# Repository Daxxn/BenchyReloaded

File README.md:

# BENCHY Version 2 - A Whole New Benchy Boi

>Alot of this is old and needs to be updated!

Your electronics workbench buddy! (Warning - Benchy is not actually your buddy and will probably try to kill you. It's hideously expensive, and way too time consuming to build!)

## Features

- Single Board Computer running embedded linux
- 5 Port USB 3.1 hub
- All data ports are **properly** protected agains over-current and backfeeding
- 2 USB 2.0 ports for the SBC peripherals (keyboard/mouse)
- 2 1Gb Ethernet ports
- 8 Software controlled relays for general things like lighting
- (In Development) Lab Power Supply W/ Current or Voltage Limiting (15V @ 2A)
- Lighting system that can drive 4 RGBW, 2 RGB, 6 dimmable, and 4 switched LED strips
- Electronic Load (5A Max)
- Simple 8 channel volt meter for quick and easy voltage testing
- (in development) Simple LCR Meter
- (in development) Function Generator

# Complete Assembly

## Motherboard Processor

This design integrates an STM32MP1 Series micro processor (U2) with 8Gb DDR3 memory (U20). This adds a large amount of raw power internally. Taking alot of the load required to control the sub-systems from the users PC and adds more flexability to the system as a whole.

## USB Hub

The main reason why I needed to design my own USB hub instead of stuffing an "off the shelf" hub up benchys trumpet was the absolute lack of protection circuitry in most "consumer grade" USB hubs. There is no back-feed protection, verry little to no current monitoring, and the bare minimum ESD and EMI protection. Thats just not acceptable! imagine my supprise when I cracked open an $85 hub from Amazon and, after blowing out a channel, found no power management at all. The cost of finding a hub that has these protections is going to be around the same price as designing and building my own. (Except for the time investment... but who cares about that?!?)

These features arent exaclty flashy, they dont look very good on a brochure. So they usually arent there. If they are, its just a bullet point. Often they just _claim_ to conform to the USB spec. The lack protection doesn't actually conform to the spec at all. I will admit, some of the protection features are optional and not necessary for every day use. The problem is an electronics workbench is very mean. It will bully these simple hubs until they don't want to play along anymore.

## I2C Bus

Im using a quite extensive I2C bus system to communicate with the different boards and functional blocks. This cuts WAY down on the number of wires and pins required for the main controller and allows for better modularity within benchy.

Due to the size of the bus and the different devices, the bus is split by an I2C Mux to keep bus integrity while communicating to far PCBs.

# Power Supply

The one thing that made the two different power supplies possible was the Switch-Mode Power Supply (SMPS) that was built into the DVR box that spawned this project. The output from the SMPS is a high-current 12V source and 30V source. This was easy to adapt to my needs.

## Adjustable supply

- 15v @ 2A
- Controlled from the motherboard or front panel

The adjustable supply is built with help from [Dave, (Thanks Dave!)](https://www.youtube.com/watch?v=CIGjActDeoM&list=PLBF35875F73B5C9B5&index=1&ab_channel=EEVblog) using the [LM317](https://rocelec.widen.net/view/pdf/mlzstqhekh/slvs044x.pdf?t.download=true&u=5oefqw) adjustable regulator.

## 5V Supply

The ATX supply can provide 15 amps to the USB ports allowing each port to supply around 2 amps. Power is managed by the [UCS2114s.](https://ww1.microchip.com/downloads/aemDocuments/documents/APID/ProductDocuments/DataSheets/UCS2114-Data-Sheet-20005743B.pdf) Controlling both the current limit and backfeeding.

# Electronic Load

Fairly standard design using a MOSFET in its linear region, dissipating alot of energy. With the help of a big heatsink and a fan, it can be used to load power supplies to test their response. The current shunt will allow for precise measurement of power usage. Control is linked to the main microcontroller on the the motherboard. Allowing full control.

# 8 Channel Volt Meter

Low voltage volt meters with moderate accuracy and speed. Designed to measure multiple voltage levels simultaneously. This is helpful for testing power supplies designed for advanced ICs that require lots of voltages to run. Such as Processors, FPGAs, and PC Motherboards.

# Function generator

Creates sine, square, and triangle waves. from ~100Hz to ~100KHz.

# 8 Mains Rated Relays

8 channel relay block used to control general things around the bench like lighting and other small devices. Rated for mains voltage but not for high current.

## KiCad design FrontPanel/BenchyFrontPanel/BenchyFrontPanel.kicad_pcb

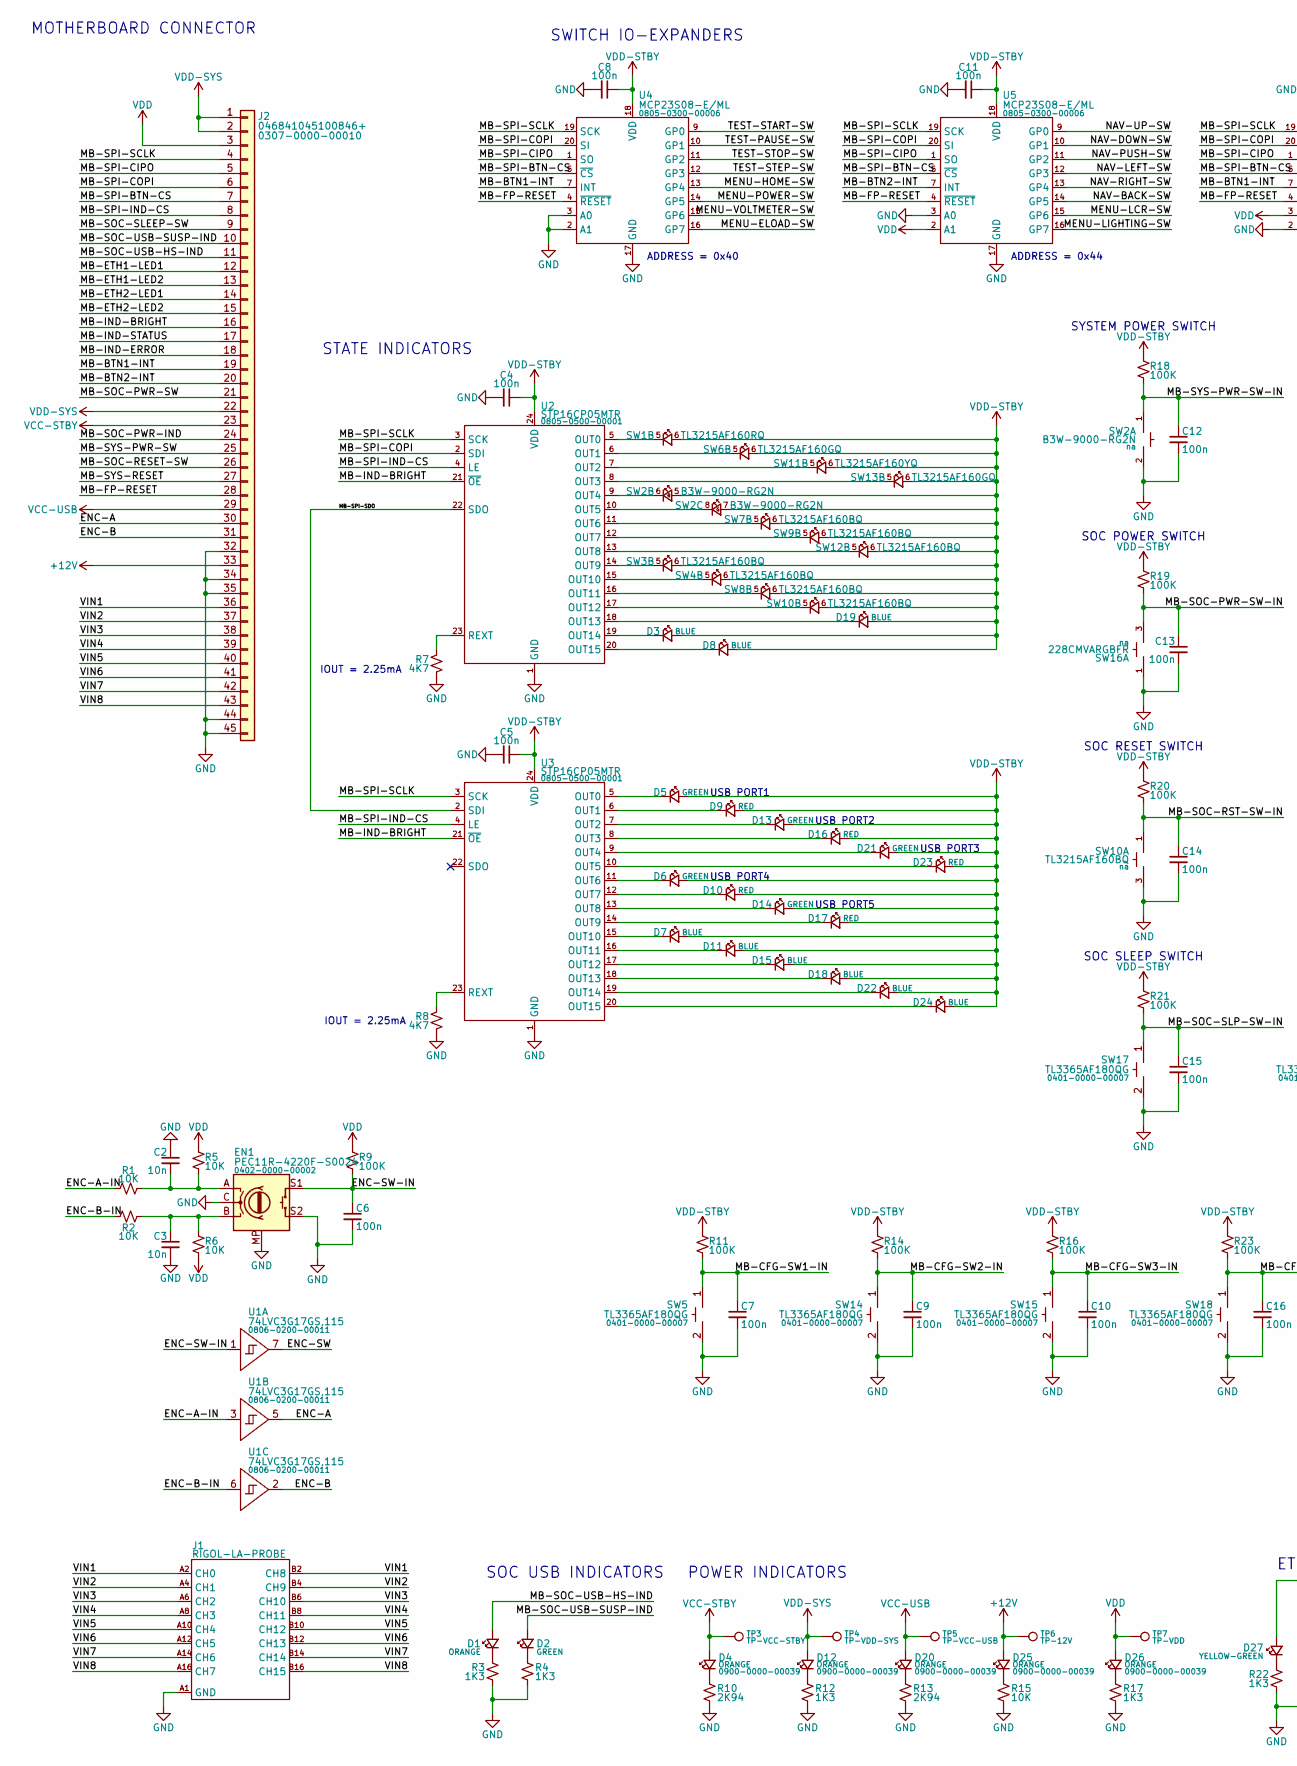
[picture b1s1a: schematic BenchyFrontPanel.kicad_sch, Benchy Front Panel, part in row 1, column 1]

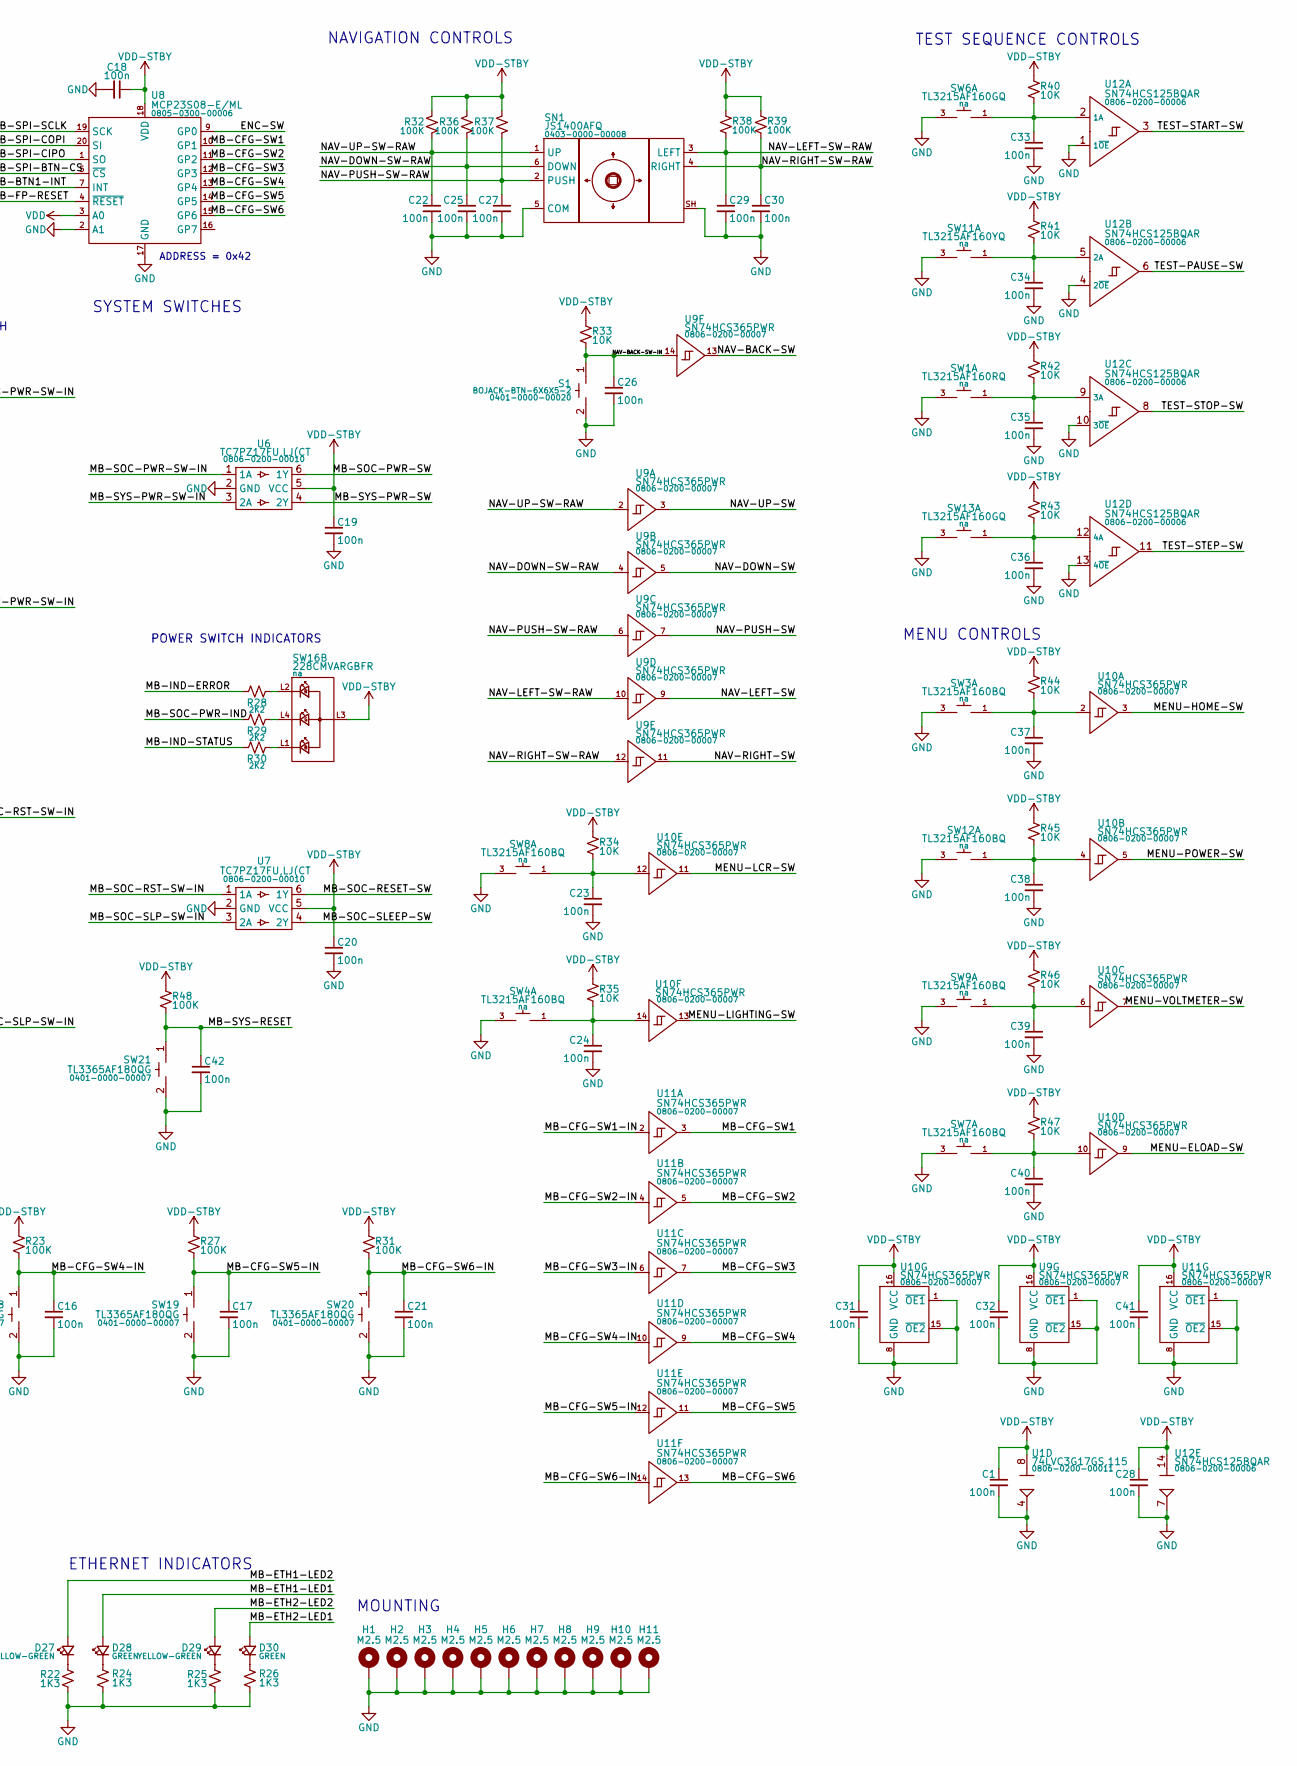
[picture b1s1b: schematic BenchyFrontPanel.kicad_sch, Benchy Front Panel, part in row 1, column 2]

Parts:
C1, C4, C5, C6, C7, C8, C9, C10, C11, C12, C13, C14, C15, C16, C17, C18, C19, C20, C21, C22, C23, C24, C25, C26, C27, C28, C29, C30, C31, C32, C33, C34, C35, C36, C37, C38, C39, C40, C41, C42: 100n; CAP_0402; PartNumber 0201-0100-00086
C2, C3: 10n; CAP_0402; PartNumber 0201-0100-00031
D1, D4, D12, D20, D25, D26: CZ3-0603-ORANGE; LED_0603_1608Metric; PartNumber 0900-0000-00039
D2, D5, D6, D13, D14, D21, D28, D30: CZ2-0603-GREEN; LED_0603_1608Metric; PartNumber 0900-0000-00038
D3, D7, D8, D11, D15, D18, D19, D22, D24: CZ1-0603-BLUE; LED_0603_1608Metric; PartNumber 0900-0000-00037
D9, D10, D16, D17, D23: CZ5-0603-RED; LED_0603_1608Metric; PartNumber 0900-0000-00041
D27, D29: CZ8-0603-YLW-GREEN; LED_0603_1608Metric; PartNumber 0900-0000-00044
EN1: PEC11R-4220F-S0024; PEC11R; PartNumber 0402-0000-00002
H1, H2, H3, H4, H5, H6, H7, H8, H9, H10, H11: M2.5; MountingHole_2.7mm_M2.5_ISO7380_Pad
J1: RIGOL-LA-PROBE; 10018784-10200TLF; PartNumber na
J2: 046841045100846+; PartNumber 0307-0000-00010
R1, R2, R5, R6, R15, R33, R34, R35, R40, R41, R42, R43, R44, R45, R46, R47: 10K; RES_0402; PartNumber 0204-0000-00016
R3, R4, R12, R17, R22, R24, R25, R26: 1K3; RES_0402; PartNumber 0204-0000-00004
R7, R8: 4K7; RES_0402; PartNumber 0204-0000-00068
R9, R11, R14, R16, R18, R19, R20, R21, R23, R27, R31, R32, R36, R37, R38, R39, R48: 100K; RES_0402; PartNumber 0204-0000-00013
R10, R13: 2K94; RES_0402; PartNumber 0204-0000-00039
R28, R29, R30: 2K2; RES_0402; PartNumber 0204-0000-00033
S1: BOJACK-BTN-6X6X5-2; BOJACK-BTN-6x6x5; PartNumber 0401-0000-00020
SN1: JS1400AFQ; JS1400; PartNumber 0403-0000-00008
SW1: TL3215AF160RQ; TL3215A; PartNumber na
SW2: B3W-9000-RG2N; B3W-9000; PartNumber na
SW3, SW4, SW7, SW8, SW9, SW10, SW12: TL3215AF160BQ; TL3215A; PartNumber na
SW5, SW14, SW15, SW17, SW18, SW19, SW20, SW21: TL3365AF180QG; PartNumber 0401-0000-00007
SW6, SW13: TL3215AF160GQ; TL3215A; PartNumber na
SW11: TL3215AF160YQ; TL3215A; PartNumber na
SW16: 228CMVARGBFR; 228C; PartNumber na
TP3: TP-VCC-STBY; TestPoint_Pad_D2.0mm; PartNumber na
TP4: TP-VDD-SYS; TestPoint_Pad_D2.0mm; PartNumber na
TP5: TP-VCC-USB; TestPoint_Pad_D2.0mm; PartNumber na
TP6: TP-12V; TestPoint_Pad_D2.0mm; PartNumber na
TP7: TP-VDD; TestPoint_Pad_D2.0mm; PartNumber na
U1: 74LVC3G17GS,115; X2SON-8_1.4x1mm_P0.35mm; PartNumber 0806-0200-00011
U2, U3: STP16CP05MTR; SOIC-24W_7.5x15.4mm_P1.27mm; PartNumber 0805-0500-00001
U4, U5, U8: MCP23S08-E/ML; QFN-20-1EP_4x4mm_P0.5mm_EP2.7x2.7mm; PartNumber 0805-0300-00006
U6, U7: TC7PZ17FU,LJ(CT; SOT-363_SC-70-6; PartNumber 0806-0200-00010
U9, U10, U11: SN74HCS365PWR; TSSOP-16_4.4x5mm_P0.65mm; PartNumber 0806-0200-00007
U12: SN74HCS125BQAR; WQFN-14_B3x2.5mm_P0.5mm; PartNumber 0806-0200-00006

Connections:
+12V: D25.2 (A), J2.33, TP6.1 (TP)
/ENC-A: J2.30, U1.5 (2Y)
/ENC-A-IN: R1.1, U1.3 (2A)
/ENC-B: J2.31, U1.2 (3Y)
/ENC-B-IN: R2.1, U1.6 (3A)
/ENC-SW: U1.7 (1Y), U8.9 (GP0)
/ENC-SW-IN: C6.1, EN1.S1, R9.2, U1.1 (1A)
/MB-BTN1-INT: J2.19, U4.7 (INT), U8.7 (INT)
/MB-BTN2-INT: J2.20, U5.7 (INT)
/MB-CFG-SW1: U8.10 (GP1), U11.3 (Y1)
/MB-CFG-SW1-IN: C7.1, R11.2, SW5.1, U11.2 (A1)
/MB-CFG-SW2: U8.11 (GP2), U11.5 (Y2)
/MB-CFG-SW2-IN: C9.1, R14.2, SW14.1, U11.4 (A2)
/MB-CFG-SW3: U8.12 (GP3), U11.7 (Y3)
/MB-CFG-SW3-IN: C10.1, R16.2, SW15.1, U11.6 (A3)
/MB-CFG-SW4: U8.13 (GP4), U11.9 (Y4)
/MB-CFG-SW4-IN: C16.1, R23.2, SW18.1, U11.10 (A4)
/MB-CFG-SW5: U8.14 (GP5), U11.11 (Y5)
/MB-CFG-SW5-IN: C17.1, R27.2, SW19.1, U11.12 (A5)
/MB-CFG-SW6: U8.15 (GP6), U11.13 (Y6)
/MB-CFG-SW6-IN: C21.1, R31.2, SW20.1, U11.14 (A6)
/MB-ETH1-LED1: D28.2 (A), J2.12
/MB-ETH1-LED2: D27.2 (A), J2.13
/MB-ETH2-LED1: D30.2 (A), J2.14
/MB-ETH2-LED2: D29.2 (A), J2.15
/MB-FP-RESET: J2.28, U4.4 (~RESET), U5.4 (~RESET), U8.4 (~RESET)
/MB-IND-BRIGHT: J2.16, U2.21 (~OE), U3.21 (~OE)
/MB-IND-ERROR: J2.18, R28.1
/MB-IND-STATUS: J2.17, R30.1
/MB-SOC-PWR-IND: J2.24, R29.1
/MB-SOC-PWR-SW: J2.21, U6.6 (1Y)
/MB-SOC-PWR-SW-IN: C13.1, R19.2, SW16.3 (SWB), SW16.4 (SWB), U6.1 (1A)
/MB-SOC-RESET-SW: J2.26, U7.6 (1Y)
/MB-SOC-RST-SW-IN: C14.1, R20.2, SW10.1 (SWA), SW10.2 (SWA), U7.1 (1A)
/MB-SOC-SLEEP-SW: J2.9, U7.4 (2Y)
/MB-SOC-SLP-SW-IN: C15.1, R21.2, SW17.1, U7.3 (2A)
/MB-SOC-USB-HS-IND: D1.2 (A), J2.11
/MB-SOC-USB-SUSP-IND: D2.2 (A), J2.10
/MB-SPI-BTN-CS: J2.7, U4.5 (~CS), U5.5 (~CS), U8.5 (~CS)
/MB-SPI-CIPO: J2.5, U4.1 (SO), U5.1 (SO), U8.1 (SO)
/MB-SPI-COPI: J2.6, U2.2 (SDI), U4.20 (SI), U5.20 (SI), U8.20 (SI)
/MB-SPI-IND-CS: J2.8, U2.4 (LE), U3.4 (LE)
/MB-SPI-SCLK: J2.4, U2.3 (SCK), U3.3 (SCK), U4.19 (SCK), U5.19 (SCK), U8.19 (SCK)
/MB-SPI-SDO: U2.22 (SDO), U3.2 (SDI)
/MB-SYS-PWR-SW: J2.25, U6.4 (2Y)
/MB-SYS-PWR-SW-IN: C12.1, R18.2, SW2.1 (SWA), SW2.3 (SWA), U6.3 (2A)
/MB-SYS-RESET: C42.1, J2.27, R48.2, SW21.1
/MENU-ELOAD-SW: U4.16 (GP7), U10.9 (Y4)
/MENU-HOME-SW: U4.13 (GP4), U10.3 (Y1)
/MENU-LCR-SW: U5.15 (GP6), U10.11 (Y5)
/MENU-LIGHTING-SW: U5.16 (GP7), U10.13 (Y6)
/MENU-POWER-SW: U4.14 (GP5), U10.5 (Y2)
/MENU-VOLTMETER-SW: U4.15 (GP6), U10.7 (Y3)
/NAV-BACK-SW: U5.14 (GP5), U9.13 (Y6)
/NAV-BACK-SW-IN: C26.1, R33.2, S1.1, U9.14 (A6)
/NAV-DOWN-SW: U5.10 (GP1), U9.5 (Y2)
/NAV-DOWN-SW-RAW: C25.1, R36.2, SN1.6 (DOWN), U9.4 (A2)
/NAV-LEFT-SW: U5.12 (GP3), U9.9 (Y4)
/NAV-LEFT-SW-RAW: C29.1, R38.2, SN1.3 (LEFT), U9.10 (A4)
/NAV-PUSH-SW: U5.11 (GP2), U9.7 (Y3)
/NAV-PUSH-SW-RAW: C27.1, R37.2, SN1.2 (PUSH), U9.6 (A3)
/NAV-RIGHT-SW: U5.13 (GP4), U9.11 (Y5)
/NAV-RIGHT-SW-RAW: C30.1, R39.2, SN1.4 (RIGHT), U9.12 (A5)
/NAV-UP-SW: U5.9 (GP0), U9.3 (Y1)
/NAV-UP-SW-RAW: C22.1, R32.2, SN1.1 (UP), U9.2 (A1)
/TEST-PAUSE-SW: U4.10 (GP1), U12.6 (2Y)
/TEST-START-SW: U4.9 (GP0), U12.3 (1Y)
/TEST-STEP-SW: U4.12 (GP3), U12.11 (4Y)
/TEST-STOP-SW: U4.11 (GP2), U12.8 (3Y)
/VIN1: J1.A2 (CH0), J1.B2 (CH8), J2.36
/VIN2: J1.A4 (CH1), J1.B4 (CH9), J2.37
/VIN3: J1.A6 (CH2), J1.B6 (CH10), J2.38
/VIN4: J1.A8 (CH3), J1.B8 (CH11), J2.39
/VIN5: J1.A10 (CH4), J1.B10 (CH12), J2.40
/VIN6: J1.A12 (CH5), J1.B12 (CH13), J2.41
/VIN7: J1.A14 (CH6), J1.B14 (CH14), J2.42
/VIN8: J1.A16 (CH7), J1.B16 (CH15), J2.43
GND: C1.2, C2.1, C3.2, C4.2, C5.2, C6.2, C7.2, C8.2, C9.2, C10.2, C11.2, C12.2, C13.2, C14.2, C15.2, C16.2, C17.2, C18.2, C19.2, C20.2, C21.2, C22.2, C23.2, C24.2, C25.2, C26.2, C27.2, C28.2, C29.2, C30.2, C31.2, C32.2, C33.2, C34.2, C35.2, C36.2, C37.2, C38.2, C39.2, C40.2, C41.2, C42.2, EN1.C, EN1.MP, EN1.S2, H1.1, H2.1, H3.1, H4.1, H5.1, H6.1, H7.1, H8.1, H9.1, H10.1, H11.1, J1.A1 (GND), J1.A3 (GND), J1.A5 (GND), J1.A7 (GND), J1.A9 (GND), J1.A11 (GND), J1.A13 (GND), J1.A15 (GND), J1.A17 (GND), J1.A18 (GND), J1.B1 (GND), J1.B3 (GND), J1.B5 (GND), J1.B7 (GND), J1.B9 (GND), J1.B11 (GND), J1.B13 (GND), J1.B15 (GND), J1.B17 (GND), J1.B18 (GND), J2.32, J2.34, J2.35, J2.44, J2.45, R3.2, R4.2, R7.2, R8.2, R10.2, R12.2, R13.2, R15.2, R17.2, R22.2, R24.2, R25.2, R26.2, S1.2, SN1.5 (COM), SN1.SH, SW1.3 (SWB), SW1.4 (SWB), SW2.2 (SWB), SW2.4 (SWB), SW3.3 (SWB), SW3.4 (SWB), SW4.3 (SWB), SW4.4 (SWB), SW5.2, SW6.3 (SWB), SW6.4 (SWB), SW7.3 (SWB), SW7.4 (SWB), SW8.3 (SWB), SW8.4 (SWB), SW9.3 (SWB), SW9.4 (SWB), SW10.3 (SWB), SW10.4 (SWB), SW11.3 (SWB), SW11.4 (SWB), SW12.3 (SWB), SW12.4 (SWB), SW13.3 (SWB), SW13.4 (SWB), SW14.2, SW15.2, SW16.1 (SWA), SW16.2 (SWA), SW17.2, SW18.2, SW19.2, SW20.2, SW21.2, U1.4 (GND), U2.1 (GND), U3.1 (GND), U4.2 (A1), U4.3 (A0), U4.17 (GND), U4.21 (GND), U5.3 (A0), U5.17 (GND), U5.21 (GND), U6.2 (GND), U7.2 (GND), U8.2 (A1), U8.17 (GND), U8.21 (GND), U9.1 (~OE1), U9.8 (GND), U9.15 (~OE2), U10.1 (~OE1), U10.8 (GND), U10.15 (~OE2), U11.1 (~OE1), U11.8 (GND), U11.15 (~OE2), U12.1 (1~OE), U12.4 (2~OE), U12.7 (GND), U12.10 (3~OE), U12.13 (4~OE), U12.15 (GND)
unnamed: C2.2, EN1.A, R1.2, R5.2
unnamed: C3.1, EN1.B, R2.2, R6.1
unnamed: D1.1 (K), R3.1
unnamed: D2.1 (K), R4.1
unnamed: D3.1 (K), U2.19 (OUT14)
unnamed: D4.1 (K), R10.1
unnamed: D5.1 (K), U3.5 (OUT0)
unnamed: D6.1 (K), U3.11 (OUT6)
unnamed: D7.1 (K), U3.15 (OUT10)
unnamed: D8.1 (K), U2.20 (OUT15)
unnamed: D9.1 (K), U3.6 (OUT1)
unnamed: D10.1 (K), U3.12 (OUT7)
unnamed: D11.1 (K), U3.16 (OUT11)
unnamed: D12.1 (K), R12.1
unnamed: D13.1 (K), U3.7 (OUT2)
unnamed: D14.1 (K), U3.13 (OUT8)
unnamed: D15.1 (K), U3.17 (OUT12)
unnamed: D16.1 (K), U3.8 (OUT3)
unnamed: D17.1 (K), U3.14 (OUT9)
unnamed: D18.1 (K), U3.18 (OUT13)
unnamed: D19.1 (K), U2.18 (OUT13)
unnamed: D20.1 (K), R13.1
unnamed: D21.1 (K), U3.9 (OUT4)
unnamed: D22.1 (K), U3.19 (OUT14)
unnamed: D23.1 (K), U3.10 (OUT5)
unnamed: D24.1 (K), U3.20 (OUT15)
unnamed: D25.1 (K), R15.1
unnamed: D26.1 (K), R17.1
unnamed: D27.1 (K), R22.1
unnamed: D28.1 (K), R24.1
unnamed: D29.1 (K), R25.1
unnamed: D30.1 (K), R26.1
unnamed: SW1.5 (LED-K), U2.5 (OUT0)
unnamed: SW2.6 (LED-GK), U2.9 (OUT4)
unnamed: SW2.8 (LED-RK), U2.10 (OUT5)
unnamed: SW3.5 (LED-K), U2.14 (OUT9)
unnamed: SW4.5 (LED-K), U2.15 (OUT10)
unnamed: SW6.5 (LED-K), U2.6 (OUT1)
unnamed: SW7.5 (LED-K), U2.11 (OUT6)
unnamed: SW8.5 (LED-K), U2.16 (OUT11)
unnamed: SW9.5 (LED-K), U2.12 (OUT7)
unnamed: SW10.5 (LED-K), U2.17 (OUT12)
unnamed: SW11.5 (LED-K), U2.7 (OUT2)
unnamed: SW12.5 (LED-K), U2.13 (OUT8)
unnamed: SW13.5 (LED-K), U2.8 (OUT3)
unnamed: R30.2, SW16.L1 (LED-B)
unnamed: R29.2, SW16.L4 (LED-G)
unnamed: R28.2, SW16.L2 (LED-R)
unnamed: R7.1, U2.23 (REXT)
unnamed: R8.1, U3.23 (REXT)
unnamed: C37.1, R44.2, SW3.1 (SWA), SW3.2 (SWA), U10.2 (A1)
unnamed: C38.1, R45.2, SW12.1 (SWA), SW12.2 (SWA), U10.4 (A2)
unnamed: C39.1, R46.2, SW9.1 (SWA), SW9.2 (SWA), U10.6 (A3)
unnamed: C40.1, R47.2, SW7.1 (SWA), SW7.2 (SWA), U10.10 (A4)
unnamed: C23.1, R34.2, SW8.1 (SWA), SW8.2 (SWA), U10.12 (A5)
unnamed: C24.1, R35.2, SW4.1 (SWA), SW4.2 (SWA), U10.14 (A6)
unnamed: C33.1, R40.2, SW6.1 (SWA), SW6.2 (SWA), U12.2 (1A)
unnamed: C34.1, R41.2, SW11.1 (SWA), SW11.2 (SWA), U12.5 (2A)
unnamed: C35.1, R42.2, SW1.1 (SWA), SW1.2 (SWA), U12.9 (3A)
unnamed: C36.1, R43.2, SW13.1 (SWA), SW13.2 (SWA), U12.12 (4A)
VCC-STBY: D4.2 (A), J2.23, TP3.1 (TP)
VCC-USB: D20.2 (A), J2.29, TP5.1 (TP)
VDD: D26.2 (A), J2.3, R5.1, R6.2, R9.1, TP7.1 (TP), U5.2 (A1), U8.3 (A0)
VDD-STBY: C1.1, C4.1, C5.1, C8.1, C11.1, C18.1, C19.1, C20.1, C28.1, C31.1, C32.1, C41.1, D3.2 (A), D5.2 (A), D6.2 (A), D7.2 (A), D8.2 (A), D9.2 (A), D10.2 (A), D11.2 (A), D13.2 (A), D14.2 (A), D15.2 (A), D16.2 (A), D17.2 (A), D18.2 (A), D19.2 (A), D21.2 (A), D22.2 (A), D23.2 (A), D24.2 (A), R11.1, R14.1, R16.1, R18.1, R19.1, R20.1, R21.1, R23.1, R27.1, R31.1, R32.1, R33.1, R34.1, R35.1, R36.1, R37.1, R38.1, R39.1, R40.1, R41.1, R42.1, R43.1, R44.1, R45.1, R46.1, R47.1, R48.1, SW1.6 (LED-A), SW2.5 (LED-GA), SW2.7 (LED-RA), SW3.6 (LED-A), SW4.6 (LED-A), SW6.6 (LED-A), SW7.6 (LED-A), SW8.6 (LED-A), SW9.6 (LED-A), SW10.6 (LED-A), SW11.6 (LED-A), SW12.6 (LED-A), SW13.6 (LED-A), SW16.L3 (LED-AN), U1.8 (VCC), U2.24 (VDD), U3.24 (VDD), U4.18 (VDD), U5.18 (VDD), U6.5 (VCC), U7.5 (VCC), U8.18 (VDD), U9.16 (VCC), U10.16 (VCC), U11.16 (VCC), U12.14 (VCC)
VDD-SYS: D12.2 (A), J2.1, J2.2, J2.22, TP4.1 (TP)

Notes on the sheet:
SOC RESET SWITCH
SOC POWER SWITCH
MENU CONTROLS
IOUT = 2.25mA
MOUNTING
SYSTEM SWITCHES
ETHERNET INDICATORS
ADDRESS = 0x42
USB PORT5
SOC USB INDICATORS
SWITCH IO-EXPANDERS
NAVIGATION CONTROLS
USB PORT2
STATE INDICATORS
ADDRESS = 0x44
TEST SEQUENCE CONTROLS
SYSTEM POWER SWITCH
USB PORT3
MOTHERBOARD CONNECTOR
POWER SWITCH INDICATORS
USB PORT4
ADDRESS = 0x40
SOC SLEEP SWITCH
USB PORT1
POWER INDICATORS

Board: 2 copper layers, 174 parts (103 on the bottom side), 143 nets, no tracks yet.
